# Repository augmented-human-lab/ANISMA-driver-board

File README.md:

[ANISMA Main Repository](https://github.com/augmented-human-lab/ANISMA) 
* [ANISMA Software](https://github.com/augmented-human-lab/ANISMA-software)
* [ANISMA Controller Board](https://github.com/augmented-human-lab/ANISMA-controller-board)
* **ANISMA Driver Board** <-- You are here!

# ANISMA Driver Board

This repository provides the Eagle Project files for the ANISMA Driver Board

The Driver Board connects to an Arduino Uno as controller board. They support eight output pins that are fully controlled and can be extended by adding more Driver Boards to an I2C bus system. We use a PCA9685 16-channel LED controller in combination with four MAX14874 dual-channel push-pull drivers in order to control the current flow using pulse-width-modulation (PWM) and dynamically set the polarity (VCC, GND, HIGH-Z) for each output pin. 

# How to get the board

Using the following link you can get direct access to the Gerber files and Bill of Materials (BOM): 
https://www.pcbway.com/project/shareproject/ANISMA_Driver_Board_3e5c784f.html

If you want you can purchase the board directly including assembly via PCBWay.

# Wiring

Wire the ANISMA Controller Board with the Arduino Uno as follows: 

| Arduino Uno | ANISMA Controller Board | Power Supply (9V Battery) |
|-------------|-------------------------|---------------------------|
| SCL         | SCL                     |                           |
| SDA         | SDA                     |                           |
| 5V          | 5V                      |                           |
| GND1        | GND                     |                           |
| GND2        |                         | -                         |
|             | VSS/12V/9V              | +                         |

# Connecting your ANISMA skin deformation device to the ANISMA Driver Board
Now you can hook up your ANISMA devices to the driver board output pins. To see what pins of your ANISMA skin deformation device need to be connected to which driver board output pins, go to the Animate view in the ANISMA Software, make sure the Arduino Uno Controller Board is connected to your computer, and click "Replay with Controllerboard". Now at each node the pin number should be displayed to which to connect your device.

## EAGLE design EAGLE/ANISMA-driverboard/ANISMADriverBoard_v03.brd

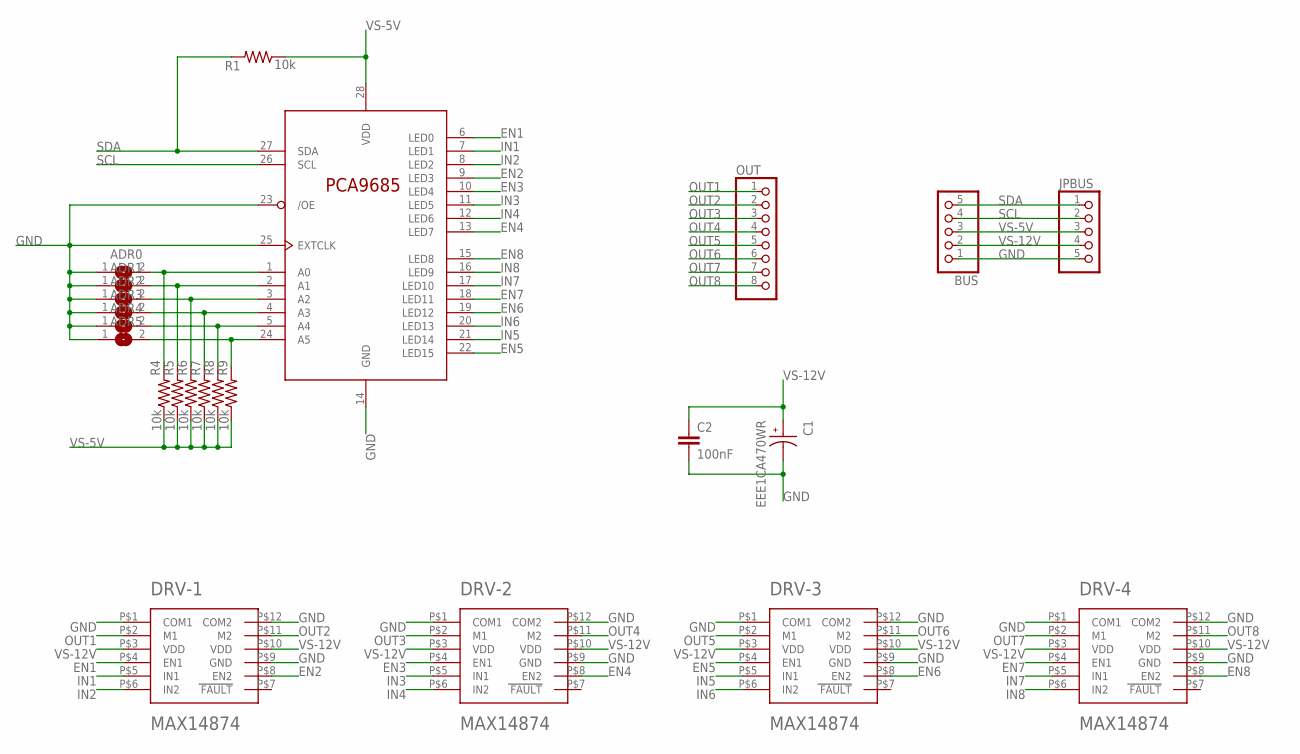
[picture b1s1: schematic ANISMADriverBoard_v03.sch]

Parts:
ADR0, ADR1, ADR2, ADR3, ADR4, ADR5: SJ
BUS: PINHD-1X5/90; 1X05/90
C1: EEE1CA470WR; CAP_EEE1CA470WR
C2: 100nF; C0603
DRV-1, DRV-2, DRV-3, DRV-4: MAX14874; TD1233
JPBUS: PINHD-1X5/90; 1X05/90
OUT: PINHD-1X8/90; 1X08/90
PCA9685: PCA9685PW; TSSOP28
R1, R4, R5, R6, R7, R8, R9: 10k; 0603

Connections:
EN1: DRV-1.P$4 (EN1), PCA9685.6 (LED0)
EN2: DRV-1.P$8 (EN2), PCA9685.9 (LED3)
EN3: DRV-2.P$4 (EN1), PCA9685.10 (LED4)
EN4: DRV-2.P$8 (EN2), PCA9685.13 (LED7)
EN5: DRV-3.P$4 (EN1), PCA9685.22 (LED15)
EN6: DRV-3.P$8 (EN2), PCA9685.19 (LED12)
EN7: DRV-4.P$4 (EN1), PCA9685.18 (LED11)
EN8: DRV-4.P$8 (EN2), PCA9685.15 (LED8)
GND: ADR0.1, ADR1.1, ADR2.1, ADR3.1, ADR4.1, ADR5.1, BUS.1, C1.2, C2.2, DRV-1.P$1 (COM1), DRV-1.P$9 (GND), DRV-1.P$12 (COM2), DRV-2.P$1 (COM1), DRV-2.P$9 (GND), DRV-2.P$12 (COM2), DRV-3.P$1 (COM1), DRV-3.P$9 (GND), DRV-3.P$12 (COM2), DRV-4.P$1 (COM1), DRV-4.P$9 (GND), DRV-4.P$12 (COM2), JPBUS.5, PCA9685.14 (GND), PCA9685.23 (/OE), PCA9685.25 (EXTCLK)
IN1: DRV-1.P$5 (IN1), PCA9685.7 (LED1)
IN2: DRV-1.P$6 (IN2), PCA9685.8 (LED2)
IN3: DRV-2.P$5 (IN1), PCA9685.11 (LED5)
IN4: DRV-2.P$6 (IN2), PCA9685.12 (LED6)
IN5: DRV-3.P$5 (IN1), PCA9685.21 (LED14)
IN6: DRV-3.P$6 (IN2), PCA9685.20 (LED13)
IN7: DRV-4.P$5 (IN1), PCA9685.17 (LED10)
IN8: DRV-4.P$6 (IN2), PCA9685.16 (LED9)
unnamed: ADR0.2, PCA9685.1 (A0), R4.2
unnamed: ADR1.2, PCA9685.2 (A1), R5.2
unnamed: ADR2.2, PCA9685.3 (A2), R6.2
unnamed: ADR3.2, PCA9685.4 (A3), R7.2
unnamed: ADR4.2, PCA9685.5 (A4), R8.2
unnamed: ADR5.2, PCA9685.24 (A5), R9.2
OUT1: DRV-1.P$2 (M1), OUT.1
OUT2: DRV-1.P$11 (M2), OUT.2
OUT3: DRV-2.P$2 (M1), OUT.3
OUT4: DRV-2.P$11 (M2), OUT.4
OUT5: DRV-3.P$2 (M1), OUT.5
OUT6: DRV-3.P$11 (M2), OUT.6
OUT7: DRV-4.P$2 (M1), OUT.7
OUT8: DRV-4.P$11 (M2), OUT.8
SCL: BUS.4, JPBUS.2, PCA9685.26 (SCL)
SDA: BUS.5, JPBUS.1, PCA9685.27 (SDA), R1.2
VS-5V: BUS.3, JPBUS.3, PCA9685.28 (VDD), R1.1, R4.1, R5.1, R6.1, R7.1, R8.1, R9.1
VS-12V: BUS.2, C1.1, C2.1, DRV-1.P$3 (VDD), DRV-1.P$10 (VDD), DRV-2.P$3 (VDD), DRV-2.P$10 (VDD), DRV-3.P$3 (VDD), DRV-3.P$10 (VDD), DRV-4.P$3 (VDD), DRV-4.P$10 (VDD), JPBUS.4

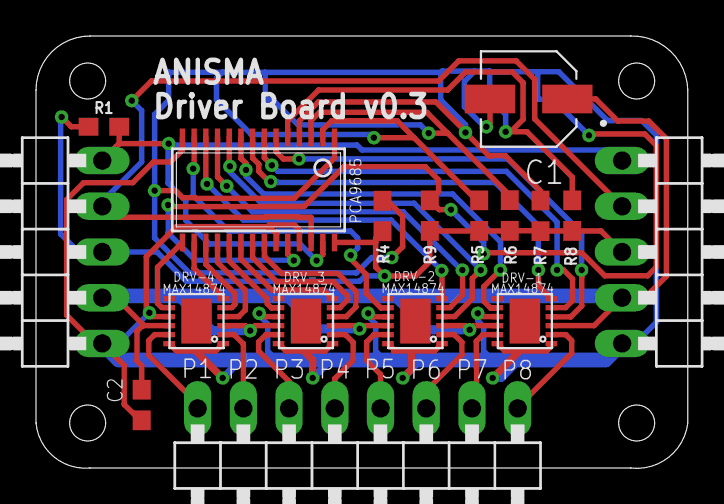
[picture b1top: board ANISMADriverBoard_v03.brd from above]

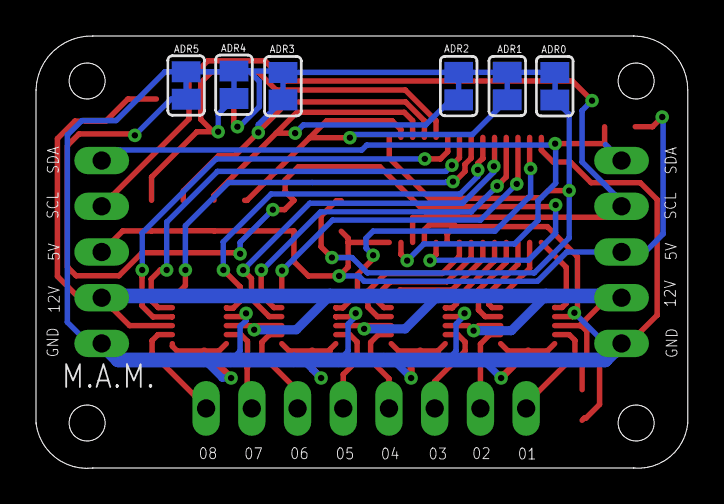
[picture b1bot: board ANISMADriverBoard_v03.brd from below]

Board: 2 copper layers, 36.2 x 24.0 mm, 23 parts (6 on the bottom side), 35 nets.

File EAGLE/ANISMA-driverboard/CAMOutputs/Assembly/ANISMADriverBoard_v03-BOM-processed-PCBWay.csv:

Item #,Designator,Qty,Manufacturer,Mfg Part #,Description / Value,Package/Footprint,Type,DigiKey Part,DigiKey URL,Your Instructions / Notes
1,"BUS, JPBUS",2,Sullins Connector Solutions,PINHD-1X5/90,,1X05/90,thru-hole,S1111E-05-ND,https://www.digikey.co.nz/en/products/detail/sullins-connect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,
2,OUT,1,Sullins Connector Solutions,PINHD-1X8/90,,1X08/90,thru-hole,S1111E-08-ND,https://www.digikey.co.nz/en/products/detail/sullins-connect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,
3,"ADR0, ADR1, ADR2, ADR3, ADR4, ADR5",6,,SJ,,SJ,SMD,,,"No assembly needed, please consider for pricing"
4,C2,1,Walsin Technology Corporation,C-EUC0603,100nF,C0603,SMD,1292-1161-2-ND,https://www.digikey.co.nz/en/products/detail/walsin-technolo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,
5,"R1, R4, R5, R6, R7, R8, R9",7,Stackpole Electronics Inc,10KOHM-0603-1/10W-1%,10k,603,SMD,RMCF0603FT10K0TR-ND,https://www.digikey.co.nz/en/products/detail/stackpole-elect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,
6,C1,1,Panasonic Electronic Components,EEE1CA470WR,EEE1CA470WR,CAP_EEE1CA470WR,SMD,PCE3890TR-ND,https://www.digikey.co.nz/en/products/detail/panasonic-elect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,
7,"DRV-1, DRV-2, DRV-3, DRV-4",4,Maxim Integrated,MAX14874,MAX14874,TD1233,SMD,175-MAX14874ETC+TTR-ND,https://www.digikey.co.nz/en/products/detail/maxim-integrate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,
8,PCA9685,1,NXP USA Inc.,PCA9685PW,PCA9685PW,TSSOP28,SMD,568-11925-2-ND,https://www.digikey.co.nz/en/products/detail/nxp-usa-inc/PCA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,

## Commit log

2021-10-01 init
2021-10-03 added big pin labels on top layer
2021-10-04 added cam and gerber files
2021-10-04 adding PCBWay BOM + Centroid File

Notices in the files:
parts and their libraries:
SparkFun-Resistors: Licensing: Creative Commons ShareAlike 4.0 International - https://creativecommons.org/licenses/by-sa/4.0
